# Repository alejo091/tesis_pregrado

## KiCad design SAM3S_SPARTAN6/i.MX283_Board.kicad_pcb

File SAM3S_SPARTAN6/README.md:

<<<<<<< HEAD
# tesis_pregrado
=======
# test
>>>>>>> 5d6981b5eae4a96473ecb7158407b447163adf92

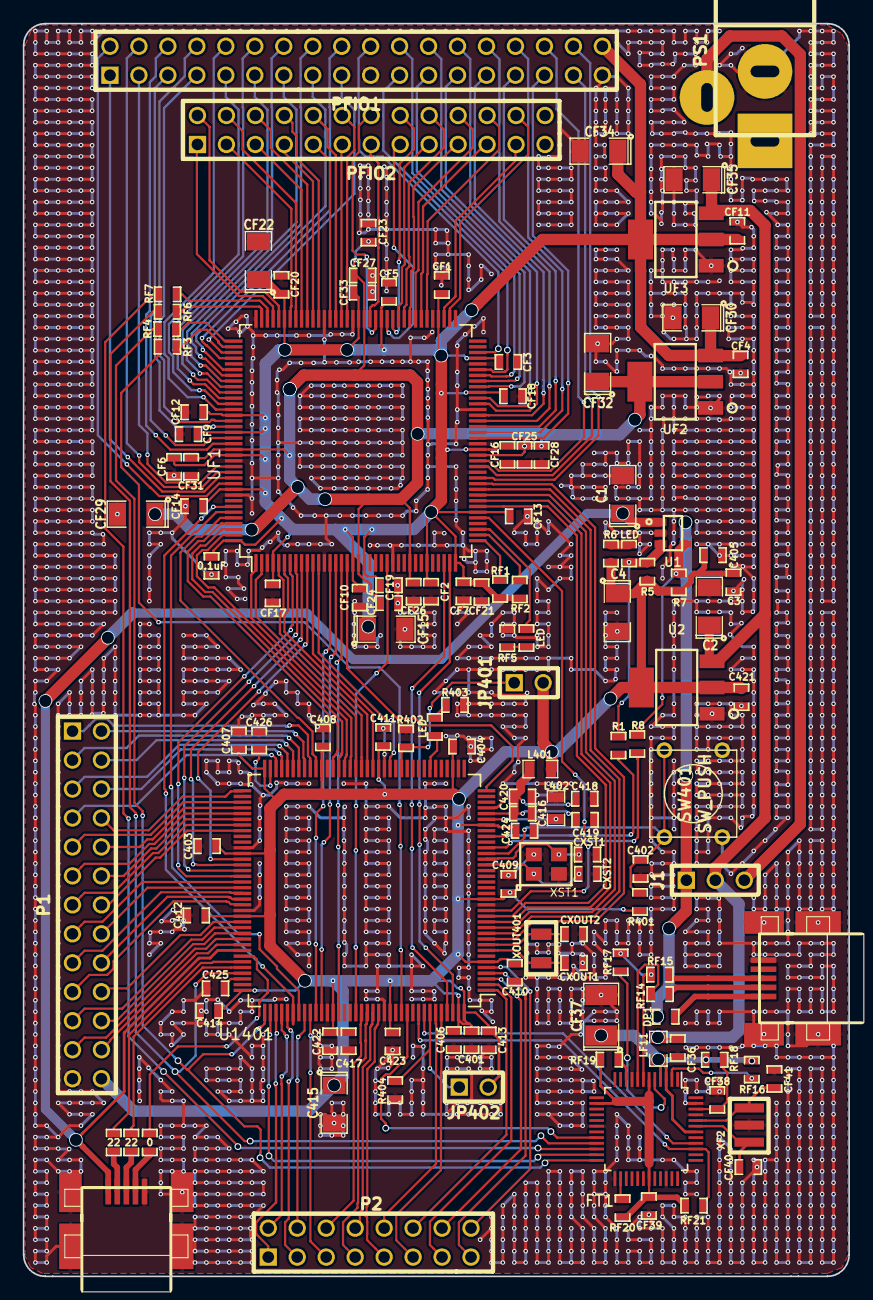
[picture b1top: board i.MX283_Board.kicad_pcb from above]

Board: 2 copper layers, 72.4 x 109.9 mm, 130 parts (0 on the bottom side), 188 nets.

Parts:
C1, C415: 4.7uF; SM1206_Opendous
C2, C4: 33uF; SM1206_Opendous
C3: 100nF; SM0603
C401, C417, C418, C419: 1uF; SM0603
C402, C403, C404, C405, C406, C407, C408, C409, C410, C411, C412, C413, C414, C416, C420, C421, C422, C423, C424: 0.1uF; SM0603
C425, C426: 2.2uF; SM0603
CF1, CF2, CF3, CF4, CF5, CF6, CF7, CF8, CF9, CF10, CF11, CF12, CF13, CF16, CF17, CF18, CF19, CF20, CF23, CF24, CF25, CF26, CF27: 0.1uF; SM0603
CF14, CF21, CF28: 1uF; SM0603
CF15, CF22, CF29: 4.7uF; SM1206_Opendous
CF30, CF32, CF34, CF35: 33uF; SM1206_Opendous
CF31, CF33: 100n; SM0603
CF36: 10nF; SM0603_Opendous
CF37: 10uF; SM1210_Opendous
CF38: 100nF; SM0603_Opendous
CF39: 33nF; SM0603_Opendous
CF40, CF41: 47pF; SM0603_Opendous
CXOUT1, CXOUT2: 6.8pF; SM0603
CXST1, CXST2: 22pF; SM0603
DF1: LED; SM0603
DP1: DIODE; SM0603_Opendous
FT1: FT2232D; LQFP-48_7x7mm_Pitch0.5mm
J1: CONN_3X1F; pin_array_1x3
J401: USB-MINI; m-pad-2.1-USB-MINI-B
JMS1: USB-MINI; m-pad-2.1-USB-MINI-B
JP401, JP402: JUMPER; pin_array_1x2
L401, L402: 2A 120 ohm; SM0805
LED1, LED2: LED; SM0603
LF11: HZ0805D152R-10; SM0805
P1: CONN_13X2; pin_array_13x2
P2: CONN_8X2; pin_array_8x2
PFIO1: CONN_02X18; pin_array_18x2
PFIO2: CONN_02X13; pin_array_13x2
PS1: BARREL_JACK; J5
R1, R2, R8: 0; SM0603
R3, R4: 22; SM0603
R5: 47K; SM0603
R6: 470; SM0603
R7, R401, R402, R404: 10K; SM0603
R403: 10k; SM0603
RF1: 47k; SM0603
RF2: 4.7k; SM0603
RF3, RF4, RF6, RF7: 68; SM0603
RF5: 1k; SM0603
RF14, RF15: 27R; SM0603_Opendous
RF16: 10K; SM0603_Opendous
RF17: 1K5; SM0603_Opendous
RF18: 470R; SM0603_Opendous
RF19, RF20: 10k; SM0603_Opendous
RF21: 15K; SM0603_Opendous
SW401: SW_PUSH; SW_PUSH_SMALL
U1: STMPS2141STR; SOT23-5
U2: ZLDO1117G33TA; SOT223
U1401: STM32F4_LQFP144; LQFP-144_20x20mm_Pitch0.5mm
UF1: XC6SLX9-2TQG144C; LQFP-144_20x20mm_Pitch0.5mm
UF2: ZLDO1117G12TA; SOT223
UF3: ZLDO1117G33TA; SOT223
XF2: 6MHz; CSTCR6M00G53Z
XOUT401: 32.768kHz; XC32.778KhZ
XST1: 12MHz; ABM8G

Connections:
3V3: C3.1, C4.1, C401.1, C403.1, C404.1, C405.1, C406.1, C407.1, C408.1, C409.1, C410.1, C411.1, C412.1, C413.1, C414.1, C415.1, C417.1, C421.1, C422.1, C423.1, C424.1, JP401.2, JP402.2, L401.1, P1.26, R5.1, R6.1, R7.2, R401.1, U2.2, U2.4, U1401.6, U1401.17, U1401.30, U1401.39, U1401.52, U1401.62, U1401.72, U1401.84, U1401.95, U1401.108, U1401.121, U1401.131, U1401.143, U1401.144
+1V2: CF23.1, CF24.1, CF25.1, CF26.1, CF27.1, CF28.1, CF29.1, CF31.1, CF32.1, UF1.19, UF1.28, UF1.52, UF1.89, UF1.128, UF2.2, UF2.4
+3.3V: CF39.1, FT1.6, FT1.14, FT1.31, RF19.2, RF20.2, RF21.1
+3.3VDAC: CF1.1, CF2.1, CF3.1, CF4.1, CF5.1, CF6.1, CF7.1, CF8.1, CF9.1, CF10.1, CF11.1, CF12.1, CF13.1, CF14.1, CF15.1, CF16.1, CF17.1, CF18.1, CF19.1, CF20.1, CF21.1, CF22.1, CF30.1, CF33.1, CF34.1, PFIO1.36, RF1.1, RF2.1, UF1.4, UF1.18, UF1.20, UF1.31, UF1.36, UF1.42, UF1.53, UF1.63, UF1.69, UF1.76, UF1.86, UF1.90, UF1.103, UF1.122, UF1.125, UF1.129, UF1.135, UF1.144, UF2.3, UF3.2, UF3.4
+5V: C2.1, CF35.1, CF36.1, J1.2, LF11.1, U2.3, UF3.3
+5VA: CF37.1, FT1.3, FT1.4, FT1.42, LF11.2, RF16.1, RF18.2
/STM32F4/AS0: U1401.10, UF1.47
/STM32F4/AS1: U1401.11, UF1.46
/STM32F4/AS2: U1401.12, UF1.45
/STM32F4/AS3: U1401.13, UF1.44
/STM32F4/AS4: U1401.14, UF1.43
/STM32F4/AS5: U1401.15, UF1.41
/STM32F4/AS6: U1401.50, UF1.12
/STM32F4/AS7: U1401.53, UF1.11
/STM32F4/AS8: U1401.54, UF1.6
/STM32F4/AS9: U1401.55, UF1.5
/STM32F4/AS10: U1401.56, UF1.2
/STM32F4/AS11: U1401.57, UF1.1
/STM32F4/AS12: U1401.87, UF1.8
/STM32F4/AS13: U1401.88, UF1.7
/STM32F4/BOOT0: JP402.1, R404.2, U1401.138
/STM32F4/BOOT1: JP401.1, R402.2, U1401.48
/STM32F4/CS: U1401.125, UF1.24
/STM32F4/DM: R4.2, U1401.103
/STM32F4/DP: R3.2, U1401.104
/STM32F4/DS0: U1401.85, UF1.10
/STM32F4/DS1: U1401.86, UF1.9
/STM32F4/DS2: U1401.114, UF1.138
/STM32F4/DS3: U1401.115, UF1.139
/STM32F4/DS4: U1401.58, UF1.143
/STM32F4/DS5: U1401.59, UF1.142
/STM32F4/DS6: U1401.60, UF1.141
/STM32F4/DS7: U1401.63, UF1.140
/STM32F4/GPIO1: P2.12, U1401.1
/STM32F4/GPIO2: P2.13, U1401.2
/STM32F4/GPIO3: P2.14, U1401.3
/STM32F4/GPIO4: P2.15, U1401.4
/STM32F4/GPIO5: P2.16, U1401.5
/STM32F4/GPIO11: P1.1, U1401.64
/STM32F4/GPIO12: P1.2, U1401.65
/STM32F4/GPIO13: P1.3, U1401.66
/STM32F4/GPIO14: P1.4, U1401.67
/STM32F4/GPIO15: P1.5, U1401.68
/STM32F4/GPIO16: P1.9, U1401.75
/STM32F4/GPIO17: P1.10, U1401.76
/STM32F4/GPIO18: P1.15, U1401.89
/STM32F4/GPIO19: P1.16, U1401.90
/STM32F4/GPIO20: P1.17, U1401.91
/STM32F4/GPIO21: P1.18, U1401.92
/STM32F4/GPIO22: P1.19, U1401.93
/STM32F4/GPIO23: P1.22, U1401.98
/STM32F4/GPIO25: P2.6, U1401.126
/STM32F4/GPIO26: P2.7, U1401.127
/STM32F4/GPIO27: P2.8, U1401.128
/STM32F4/GPIO28: P2.9, U1401.129
/STM32F4/GPIO30: P2.4, U1401.116
/STM32F4/GPIO31: P2.5, U1401.117
/STM32F4/GPIO34: P1.13, U1401.79
/STM32F4/GPIO35: P1.14, U1401.80
/STM32F4/GPIO40: P1.23, U1401.99
/STM32F4/I2C1_SCL: P2.10, U1401.139
/STM32F4/I2C1_SDA: P2.11, U1401.140
/STM32F4/ID: R2.2, U1401.102
/STM32F4/IO5: P1.8, U1401.73
/STM32F4/IO6: P1.6, U1401.69
/STM32F4/IO7: P1.7, U1401.70
/STM32F4/IO8: P1.24, U1401.100
/STM32F4/JTDI: FT1.23, U1401.110
/STM32F4/LED1: LED1.1, U1401.43
/STM32F4/NBL0: U1401.141, UF1.34
/STM32F4/NBL1: U1401.142, UF1.35
/STM32F4/NJTRST: FT1.20, U1401.134
/STM32F4/NOE: U1401.118, UF1.14
/STM32F4/NRST: C402.1, R401.2, SW401.1, U1401.25
/STM32F4/NWAIT: U1401.122, UF1.16
/STM32F4/NWE: U1401.119, UF1.15
/STM32F4/SPI_MISO: P2.2, U1401.112
/STM32F4/SPI_MOSI: P2.3, U1401.113
/STM32F4/SPI_SCK: P2.1, U1401.111
/STM32F4/UA3_RX: P1.12, U1401.78
/STM32F4/UA3_TX: P1.11, U1401.77
/STM32F4/UA_RX: P1.21, U1401.97
/STM32F4/UA_TX: P1.20, U1401.96
/STM32F4/VBUS: C1.1, J401.1, U1.1, U1401.101
/STM32F4/VREF: C416.1, C418.1, C419.1, C420.1, L401.2, U1401.32, U1401.33
/STM32F4/~EN: R8.1, U1401.26
/STM32F4/~FAULT: R1.2, U1401.28
/serial_interface/RXD: FT1.39, RF21.2, U1401.136
/serial_interface/TXD: FT1.40, U1401.137
/spartan6/CLK_FPGA: U1401.36, UF1.17
/spartan6/F_TCK: FT1.24, RF4.1, U1401.109
/spartan6/F_TDI: RF3.1, U1401.133
/spartan6/F_TDO: FT1.22, RF7.1
/spartan6/F_TMS: FT1.21, RF6.1, U1401.105
/spartan6/IO16: DF1.1, UF1.39
/spartan6/IO17: PFIO1.34, UF1.48
/spartan6/IO18: PFIO1.33, UF1.50
/spartan6/IO19: PFIO1.32, UF1.51
/spartan6/IO20: PFIO1.31, UF1.55
/spartan6/IO21: PFIO1.30, UF1.56
/spartan6/IO22: PFIO1.29, UF1.57
/spartan6/IO23: PFIO1.28, UF1.58
/spartan6/IO24: PFIO1.27, UF1.59
/spartan6/IO25: PFIO1.26, UF1.61
/spartan6/IO26: PFIO1.25, UF1.62
/spartan6/IO27: PFIO1.24, UF1.64
/spartan6/IO28: PFIO1.23, UF1.65
/spartan6/IO29: PFIO1.22, UF1.66
/spartan6/IO30: PFIO1.21, UF1.67
/spartan6/IO31: PFIO1.20, UF1.70
/spartan6/IO32: PFIO2.24, UF1.74
/spartan6/IO33: PFIO2.23, UF1.75
/spartan6/IO34: PFIO2.22, UF1.78
/spartan6/IO35: PFIO2.21, UF1.79
/spartan6/IO36: PFIO2.20, UF1.80
/spartan6/IO37: PFIO2.19, UF1.81
/spartan6/IO38: PFIO2.18, UF1.82
/spartan6/IO39: PFIO2.17, UF1.83
/spartan6/IO40: PFIO2.16, UF1.84
/spartan6/IO41: PFIO2.15, UF1.85
/spartan6/IO42: PFIO2.14, UF1.87
/spartan6/IO43: PFIO2.13, UF1.88
/spartan6/IO44: PFIO2.12, UF1.92
/spartan6/IO45: PFIO2.11, UF1.93
/spartan6/IO46: PFIO2.10, UF1.94
/spartan6/IO47: PFIO2.9, UF1.95
/spartan6/IO48: PFIO2.8, UF1.97
/spartan6/IO49: PFIO2.7, UF1.98
/spartan6/IO50: PFIO2.6, UF1.99
/spartan6/IO51: PFIO2.5, UF1.100
/spartan6/IO52: PFIO2.4, UF1.101
/spartan6/IO53: PFIO2.3, UF1.102
/spartan6/IO54: PFIO2.2, UF1.104
/spartan6/IO55: PFIO2.1, UF1.105
/spartan6/IO56: PFIO1.17, UF1.111
/spartan6/IO57: PFIO1.18, UF1.112
/spartan6/IO58: PFIO1.15, UF1.114
/spartan6/IO59: PFIO1.16, UF1.115
/spartan6/IO60: PFIO1.13, UF1.116
/spartan6/IO61: PFIO1.14, UF1.117
/spartan6/IO62: PFIO1.11, UF1.118
/spartan6/IO63: PFIO1.12, UF1.119
/spartan6/IO64: PFIO1.9, UF1.120
/spartan6/IO65: PFIO1.10, UF1.121
/spartan6/IO66: PFIO1.7, UF1.123
/spartan6/IO67: PFIO1.8, UF1.124
/spartan6/IO68: PFIO1.5, UF1.126
/spartan6/IO69: PFIO1.6, UF1.127
/spartan6/IO70: PFIO1.3, UF1.131
/spartan6/IO71: PFIO1.4, UF1.132
/spartan6/IO72: PFIO1.1, UF1.133
/spartan6/IO73: PFIO1.2, UF1.134
GND: C1.2, C2.2, C3.2, C4.2, C401.2, C402.2, C403.2, C404.2, C405.2, C406.2, C407.2, C408.2, C409.2, C410.2, C411.2, C412.2, C413.2, C414.2, C415.2, C416.2, C417.2, C418.2, C419.2, C420.2, C421.2, C422.2, C423.2, C424.2, C425.2, C426.2, CF1.2, CF2.2, CF3.2, CF4.2, CF5.2, CF6.2, CF7.2, CF8.2, CF9.2, CF10.2, CF11.2, CF12.2, CF13.2, CF14.2, CF15.2, CF16.2, CF17.2, CF18.2, CF19.2, CF20.2, CF21.2, CF22.2, CF23.2, CF24.2, CF25.2, CF26.2, CF27.2, CF28.2, CF29.2, CF30.2, CF31.2, CF32.2, CF33.2, CF34.2, CF35.2, CF36.2, CF37.2, CF38.2, CF39.2, CF40.1, CF41.1, CXOUT1.2, CXOUT2.2, CXST1.2, CXST2.2, FT1.9, FT1.18, FT1.25, FT1.34, FT1.45, FT1.47, J401.5, J401.6, J401.7, J401.8, J401.9, JMS1.5, JMS1.6, JMS1.7, JMS1.8, JMS1.9, L402.2, P1.25, PFIO1.19, PFIO1.35, PS1.2, R402.1, R403.2, R404.1, RF5.1, SW401.2, U1.2, U2.1, U1401.16, U1401.38, U1401.51, U1401.61, U1401.83, U1401.94, U1401.107, U1401.120, U1401.130, UF1.3, UF1.13, UF1.25, UF1.49, UF1.54, UF1.60, UF1.68, UF1.77, UF1.91, UF1.96, UF1.108, UF1.113, UF1.130, UF1.136, UF2.1, UF3.1, XF2.2, XST1.2, XST1.4
unnamed: C425.1, U1401.106
unnamed: C426.1, U1401.71
unnamed: CF38.1, FT1.46, RF18.1
unnamed: CF40.2, FT1.43, XF2.1
unnamed: CF41.2, FT1.44, XF2.3
unnamed: CXOUT1.1, U1401.8, XOUT401.1
unnamed: CXOUT2.1, U1401.9, XOUT401.2
unnamed: CXST1.1, U1401.24, XST1.3
unnamed: CXST2.1, U1401.23, XST1.1
unnamed: DF1.2, RF5.2
unnamed: DP1.1, JMS1.1
unnamed: FT1.2, RF16.2
unnamed: FT1.5, RF17.2
unnamed: FT1.7, RF15.2, RF17.1
unnamed: FT1.8, RF14.2
unnamed: FT1.10, RF19.1
unnamed: FT1.26, RF20.1
unnamed: J401.2, R4.1
unnamed: J401.3, R3.1
unnamed: J401.4, R2.1
unnamed: JMS1.2, RF14.1
unnamed: JMS1.3, RF15.1
unnamed: L402.1, U1401.31
unnamed: LED1.2, R403.1
unnamed: LED2.1, R6.2
unnamed: LED2.2, R1.1, R5.2, U1.3
unnamed: R7.1, R8.2, U1.4
unnamed: RF1.2, UF1.37
unnamed: RF2.2, UF1.38
unnamed: RF3.2, UF1.110
unnamed: RF4.2, UF1.109
unnamed: RF6.2, UF1.107
unnamed: RF7.2, UF1.106
VDD4P2: J1.3, PS1.1
VDD5V: DP1.2, J1.1, U1.5

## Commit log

2015-05-19 Initial commit with contributors
2015-05-19 Modifying digital_board, removing, imx283, adding ftdi circuit
2015-05-19 Routing
2015-05-20 Routing almost finished
2015-05-21 Finishing routing, adding gerber files
2015-07-07 Updating BOM
2015-09-16 Adding Examples and configuration files
2015-09-16 Adding installation guides for xc3sprog and openocd
2015-10-21 Updating BOM with costs and references
2015-10-21 Adding xc3sprog code
2016-04-22 Added files via upload
